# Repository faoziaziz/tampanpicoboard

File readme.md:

# TampanTech Pico

## Deskrispi

Ini adalah repository tampanboard pico. 

# Screenshoot

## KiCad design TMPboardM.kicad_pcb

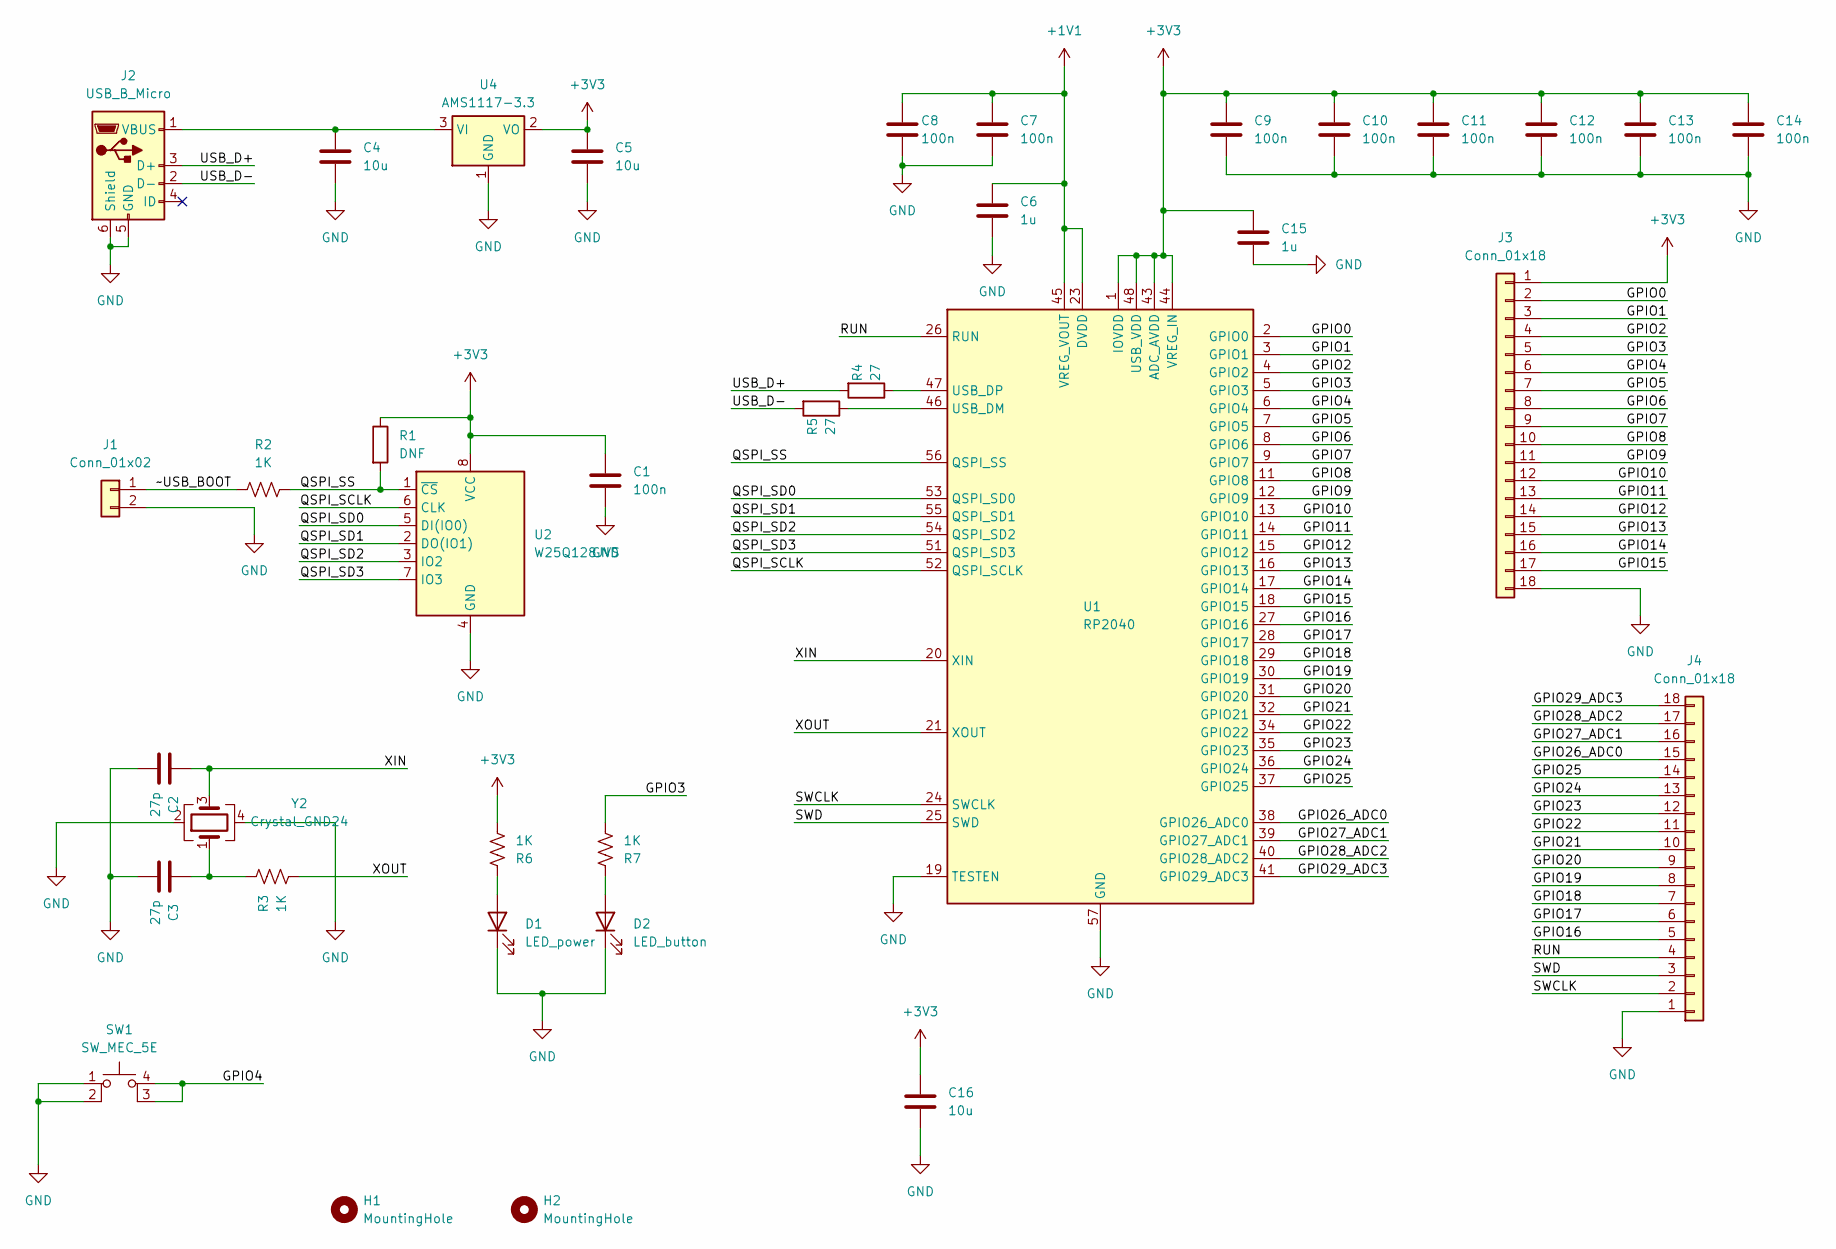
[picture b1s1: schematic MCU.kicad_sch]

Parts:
C1, C7, C8, C9, C10, C11, C12, C13, C14: 100n; C_0201_0603Metric_Pad0.64x0.40mm_HandSolder
C2, C3: 27p; C_0201_0603Metric_Pad0.64x0.40mm_HandSolder
C4, C5, C16: 10u; C_0402_1005Metric_Pad0.74x0.62mm_HandSolder
C6, C15: 1u; C_0201_0603Metric_Pad0.64x0.40mm_HandSolder
D1: LED_power; D_0603_1608Metric_Pad1.05x0.95mm_HandSolder
D2: LED_button; D_0603_1608Metric_Pad1.05x0.95mm_HandSolder
H1: MountingHole; MountingHole_2mm
H2: MountingHole; MountingHole_3mm
J1: Conn_01x02; PinSocket_1x02_P2.54mm_Vertical
J2: USB_B_Micro; USB_Micro-B_XKB_U254-051T-4BH83-F1S
J3, J4: Conn_01x18; PinSocket_1x18_P2.54mm_Vertical
R1: DNF; R_0201_0603Metric_Pad0.64x0.40mm_HandSolder
R2, R3, R6, R7: 1K; R_0201_0603Metric_Pad0.64x0.40mm_HandSolder
R4, R5: 27; R_0201_0603Metric_Pad0.64x0.40mm_HandSolder
SW1: SW_MEC_5E; SW_TP10721645
U1: RP2040; QFN-56-1EP_7x7mm_P0.4mm_EP3.2x3.2mm
U2: W25Q128JVS; SOIC-8_5.23x5.23mm_P1.27mm
U4: AMS1117-3.3; SOT-223-3_TabPin2
Y2: Crystal_GND24; Crystal_SMD_3225-4Pin_3.2x2.5mm_HandSoldering

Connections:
+1V1: C6.1, C7.1, C8.1, U1.23 (DVDD), U1.45 (VREG_VOUT), U1.50 (DVDD)
+3V3: C1.1, C5.1, C9.1, C10.1, C11.1, C12.1, C13.1, C14.1, C15.2, C16.1, J3.1, R1.1, R6.1, U1.1 (IOVDD), U1.10 (IOVDD), U1.22 (IOVDD), U1.33 (IOVDD), U1.42 (IOVDD), U1.43 (ADC_AVDD), U1.44 (VREG_IN), U1.48 (USB_VDD), U1.49 (IOVDD), U2.8 (VCC), U4.2 (VO)
/MicroController/GPIO0: J3.2, U1.2 (GPIO0)
/MicroController/GPIO1: J3.3, U1.3 (GPIO1)
/MicroController/GPIO2: J3.4, U1.4 (GPIO2)
/MicroController/GPIO3: J3.5, R7.1, U1.5 (GPIO3)
/MicroController/GPIO4: J3.6, SW1.3 (K), SW1.4 (A), U1.6 (GPIO4)
/MicroController/GPIO5: J3.7, U1.7 (GPIO5)
/MicroController/GPIO6: J3.8, U1.8 (GPIO6)
/MicroController/GPIO7: J3.9, U1.9 (GPIO7)
/MicroController/GPIO8: J3.10, U1.11 (GPIO8)
/MicroController/GPIO9: J3.11, U1.12 (GPIO9)
/MicroController/GPIO10: J3.12, U1.13 (GPIO10)
/MicroController/GPIO11: J3.13, U1.14 (GPIO11)
/MicroController/GPIO12: J3.14, U1.15 (GPIO12)
/MicroController/GPIO13: J3.15, U1.16 (GPIO13)
/MicroController/GPIO14: J3.16, U1.17 (GPIO14)
/MicroController/GPIO15: J3.17, U1.18 (GPIO15)
/MicroController/GPIO16: J4.5, U1.27 (GPIO16)
/MicroController/GPIO17: J4.6, U1.28 (GPIO17)
/MicroController/GPIO18: J4.7, U1.29 (GPIO18)
/MicroController/GPIO19: J4.8, U1.30 (GPIO19)
/MicroController/GPIO20: J4.9, U1.31 (GPIO20)
/MicroController/GPIO21: J4.10, U1.32 (GPIO21)
/MicroController/GPIO22: J4.11, U1.34 (GPIO22)
/MicroController/GPIO23: J4.12, U1.35 (GPIO23)
/MicroController/GPIO24: J4.13, U1.36 (GPIO24)
/MicroController/GPIO25: J4.14, U1.37 (GPIO25)
/MicroController/GPIO26_ADC0: J4.15, U1.38 (GPIO26_ADC0)
/MicroController/GPIO27_ADC1: J4.16, U1.39 (GPIO27_ADC1)
/MicroController/GPIO28_ADC2: J4.17, U1.40 (GPIO28_ADC2)
/MicroController/GPIO29_ADC3: J4.18, U1.41 (GPIO29_ADC3)
/MicroController/QSPI_SCLK: U1.52 (QSPI_SCLK), U2.6 (CLK)
/MicroController/QSPI_SD0: U1.53 (QSPI_SD0), U2.5 (DI(IO0))
/MicroController/QSPI_SD1: U1.55 (QSPI_SD1), U2.2 (DO(IO1))
/MicroController/QSPI_SD2: U1.54 (QSPI_SD2), U2.3 (IO2)
/MicroController/QSPI_SD3: U1.51 (QSPI_SD3), U2.7 (IO3)
/MicroController/QSPI_SS: R1.2, R2.2, U1.56 (QSPI_SS), U2.1 (~CS)
/MicroController/RUN: J4.4, U1.26 (RUN)
/MicroController/SWCLK: J4.2, U1.24 (SWCLK)
/MicroController/SWD: J4.3, U1.25 (SWD)
/MicroController/USB_D+: J2.3 (D+), R4.2
/MicroController/USB_D-: J2.2 (D-), R5.2
/MicroController/XIN: C2.2, U1.20 (XIN), Y2.3
/MicroController/XOUT: R3.1, U1.21 (XOUT)
/MicroController/~USB_BOOT: J1.1, R2.1
GND: C1.2, C2.1, C3.1, C4.2, C5.2, C6.2, C7.2, C8.2, C9.2, C10.2, C11.2, C12.2, C13.2, C14.2, C15.1, C16.2, D1.1 (K), D2.1 (K), J1.2, J2.5 (GND), J2.6 (Shield), J3.18, J4.1, SW1.1, SW1.2, U1.19 (TESTEN), U1.57 (GND), U2.4 (GND), U4.1 (GND), Y2.2, Y2.4
unnamed: C3.2, R3.2, Y2.1
unnamed: D1.2 (A), R6.2
unnamed: D2.2 (A), R7.2
unnamed: C4.1, J2.1 (VBUS), U4.3 (VI)
unnamed: R5.1, U1.46 (USB_DM)
unnamed: R4.1, U1.47 (USB_DP)

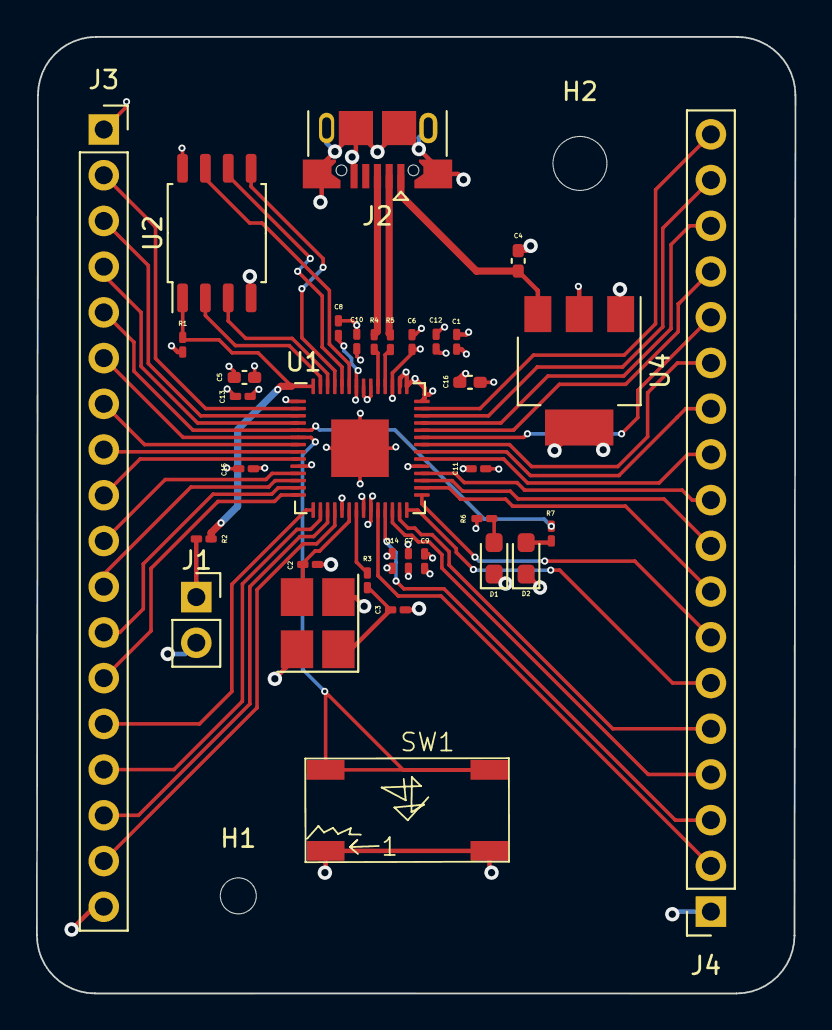
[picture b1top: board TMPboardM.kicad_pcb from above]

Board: 4 copper layers, 42.1 x 53.1 mm, 36 parts (0 on the bottom side), 53 nets.

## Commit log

2023-07-05 tampanpico
2023-07-05 mantap
